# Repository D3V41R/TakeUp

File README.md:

# TakeUp

**TakeUp** is a custom quadrotor flight stack built from scratch: a hand-wired STM32F4 flight controller, a self-etched power distribution board, a bit-banged NRF24L01+ radio link, and a from-scratch DShot150 ESC driver. The end goal is voice-controlled flight — commands transmitted over audio instead of a stick input — with the current build flying on a manual PS5-controller-over-RF link while the audio pipeline is developed.

> **Status: in progress.** Attitude estimation, the RF link, and standard PWM motor control are working. DShot150 and voice control are active work-in-progress (see [Known Limitations](#known-limitations--todo)).

---

## Table of Contents

- [System Overview](#system-overview)
- [Repository Layout](#repository-layout)
- [Flight Controller (STM32F4)](#flight-controller-stm32f4)
- [IMU / Attitude Estimation (MPU6050)](#imu--attitude-estimation-mpu6050)
- [Wireless Link (NRF24L01+)](#wireless-link-nrf24l01)
- [Motor Control](#motor-control)
- [Custom DShot150 Driver](#custom-dshot150-driver)
- [Power Distribution Board](#power-distribution-board)
- [Building the Firmware](#building-the-firmware)
- [Known Limitations / TODO](#known-limitations--todo)
- [License](#license)

---

## System Overview

Today, the RC packet source is a PS5 controller relayed through an ESP32 (`Software/Src/esp32.c`) rather than voice — this is the interim control path used to validate the flight controller, IMU fusion, and radio link while the voice front-end is built out.

---

## Repository Layout

```
TakeUp/
├── Hardware/
│   └── BMS/
│       ├── DroneBMS.kicad_sch     # power distribution board schematic (KiCad 9)
│       ├── DroneBMS.kicad_pcb     # 4-layer PCB layout
│       └── PCB_Render_1.png       # 3D render
│   └── Flight Controller/
│       └── IMG_4678.jpeg          # hand-soldered flight controller build
├── Software/
│   ├── INC/                       # headers
│   │   ├── Dshot150.h
│   │   ├── Motors.h
│   │   ├── Nrf2401.h
│   │   ├── mpu6050.h
│   │   └── main.h
│   └── Src/
│       ├── Dshot150.c              # custom DShot150 frame builder + DMA-PWM transmit
│       ├── Motors.c                # standard 1000-2000us PWM ESC control
│       ├── Nrf2401.c                # bare-register NRF24L01+ driver (no external RF24 lib)
│       ├── mpu6050.c                # IMU driver + complementary filter
│       ├── esp32.c                  # ESP32 transmitter sketch (PS5 controller → NRF24)
│       └── main.c                   # flight controller entry point / RX loop
└── image.png                        # power board schematic export
```

---

## Flight Controller (STM32F4)

The flight controller runs on an STM32F4 Nucleo-64 board (pin map matches the standard Nucleo layout: `PC13` user button, `PA5` = `LD2`). Firmware is generated with STM32CubeMX/HAL and hand-extended.

*Hand-wired prototype: MPU6050 breakout and NRF24L01+ (with SMA antenna) soldered onto perfboard with screw-terminal breakouts for power and signal.*

**Clock tree:** 8 MHz HSE → PLL (`M=4, N=72, P=/2`) → 72 MHz SYSCLK, APB1 = 36 MHz (72 MHz timer clock), APB2 = 72 MHz.

**Peripherals in use:**

| Peripheral | Role | Pins |
|---|---|---|
| `I2C1` | MPU6050 IMU, 100 kHz standard mode | `PB6` = SCL, `PB7` = SDA |
| `SPI2` | NRF24L01+ radio, mode 0, `fPCLK/2` | `PB14` = MISO, `PB15` = MOSI, `PC7` = SCK |
| — | NRF24 chip-select / chip-enable (bit-banged GPIO, not SPI NSS) | `PC0` = CSN, `PB0` = CE |
| `TIM2` (4ch) | ESC PWM / DShot output | `PA0` = CH1 (active), `PA1` = CH2, `PB10` = CH3, `PB2` = CH4 (configured, unused) |
| `USART2` | Debug/telemetry console, 115200 8N1 | `PA2` = TX, `PA3` = RX |

Boot sequence (`main.c`): GPIO → USART2 → I2C1 → SPI2 → TIM2 → arm ESC (`Motor_Init`) → bring up radio (`Nrf_init`) → enter RX loop, printing `BOOT`/`I2C OK`/`SPI OK`/`TIM OK` over UART at each stage so a bring-up failure is localized immediately from the serial log.

---

## IMU / Attitude Estimation (MPU6050)

`mpu6050.c` talks to the MPU6050 directly over `I2C1` (no external library) at address `0x68`.

**Init sequence:**

| Register | Value | Purpose |
|---|---|---|
| `0x75` (`WHO_AM_I`) | read, expect `0x68` | sanity check on boot |
| `0x6B` (`PWR_MGMT_1`) | `0x00` | wake from sleep, select internal clock |
| `0x1A` (`CONFIG`) | `0x01` | DLPF on, ~184 Hz bandwidth |
| `0x25` (`SMPLRT_DIV`) | `0x00` | sample rate = 1 kHz / (1 + 0) = 1 kHz |
| `0x1B` (`GYRO_CONFIG`) | `0b00011000` | ±2000 °/s full scale |
| `0x1C` (`ACCEL_CONFIG`) | `0x00` | ±16 g full scale |

Raw accel/gyro burst-reads come from `0x3B` (6 bytes, accel X/Y/Z) and `0x43` (6 bytes, gyro X/Y/Z), scaled by the datasheet sensitivity for the selected range (`/16384.0f` g/LSB for accel, `/16.4f` (°/s)/LSB for gyro).

**Gyro calibration** (`calibrate_gyro`) averages 1000 samples at boot to compute a static bias — currently computed but not yet subtracted from live readings (see [Known Limitations](#known-limitations--todo)).

**Attitude fusion** (`log_data`) runs a single-stage complementary filter:

1. Exponential low-pass (`ALPHA = 0.02`) on both accel and gyro channels.
2. Body-rate → Euler-rate transform: `phiHat_rps = gx + tan(theta)*(sin(phi)*gy + cos(phi)*gz)`, `thetaHat_rps = cos(phi)*gy - sin(phi)*gz`.
3. Gyro integration at `dt = 0.001 s` (1 kHz loop assumption) added to the running angle.
4. Fusion with accel-derived tilt (`atan`/`asin` off the gravity vector) at a 0.98 / 0.05 gyro/accel blend, printed over `USART2` as `Pitch:__, Roll:__`.

---

## Wireless Link (NRF24L01+)

Both ends of the radio link are custom drivers — the STM32 side (`Nrf2401.c`) talks directly to the NRF24L01+ command/register set over `SPI2` with no radio library, and the transmit side (`esp32.c`) uses the Arduino `RF24` library on an ESP32 paired to a PS5 controller over Bluetooth.

**Link configuration (must match on both ends):**

| Setting | Value |
|---|---|
| Data rate | 1 Mbps |
| RF channel | 85 (2.485 GHz) |
| TX power | 0 dBm |
| Address width | 5 bytes (`SETUP_AW = 0x03`) |
| RX/TX address | `E7 E7 E7 E7 E7` |
| Payload size | 16 bytes, static (no dynamic payloads) |
| Auto-ACK | disabled on both ends |
| CRC | 16-bit (ESP32 side); STM32 driver disables hardware auto-ack/CRC handling and relies on the fixed packet contract instead |

**Packet format** — a flat 16-byte struct sent as raw bytes:

```c
typedef struct {
    float throttle;
    float roll;
    float pitch;
    float yaw;
} rc_packet;   // 4 x 4-byte float = 16 bytes, matches NRF24 payload size exactly
```

**TX side** (`esp32.c`): reads PS5 gamepad stick axes via `ps5Controller`, maps left stick → throttle/roll and right stick → pitch/yaw, and pushes a packet over `RF24::write()` roughly every 20 ms.

**RX side** (`Nrf2401.c` + `main.c`): `Nrf_init()` powers up the radio, configures the RF settings above, and starts listening (`CE` high). `Recieve_nrf()` polls the `STATUS` register for the `RX_DR` flag, pulls the 16-byte payload with the `R_RX_PAYLOAD` command, and clears the flag. `main.c` copies the payload into an `rc_packet`, runs the throttle channel through a first-order low-pass (`alpha = 0.1`), and feeds the result to `Motor_SetSpeed()`.

Note: `enable_auto_ack()` exists in the driver but is not currently called from `Nrf_init()` — auto-ack stays disabled to match the transmitter's `setAutoAck(false)`.

---

## Motor Control

`Motors.c` drives ESCs with standard hobby PWM on `TIM2` channel 1: with the timer clocked at 1 MHz (72 MHz / (prescaler 71 + 1)) and a 20000-tick period, `CCR1` directly represents the pulse width in **microseconds** at a 50 Hz refresh rate — the same 1000–2000 µs framing every analog PWM ESC expects.

| Function | Behavior |
|---|---|
| `Motor_Init()` | Arms the ESC: full throttle (2000) for 2 s, then minimum (1000) for 2 s, matching the standard ESC calibration/arm beep sequence |
| `Motor_SetSpeed(percent)` | Maps 0–100 % linearly to 1000–2000 µs |
| `Motor_SetRaw(ccr)` | Direct CCR write for bench testing |
| `Motor_Stop()` | Forces minimum throttle (1000) |
| `Motor_Control_UART()` | Serial bench-test command parser (`S<pct>` set speed, `R<ccr>` set raw, `X` stop) over `USART2` |

Only `TIM2_CH1` is currently wired to a motor output in `main.c` — channels 2–4 are configured (see pin table above) but not yet driven, so multi-motor mixing isn't implemented yet.

---

## Custom DShot150 Driver

`Dshot150.c` implements the DShot150 digital ESC protocol frame-by-frame, from scratch, on top of `TIM2` + DMA.

**Frame construction is spec-correct.** A DShot frame is 16 bits: 11-bit throttle value, 1 telemetry-request bit, and a 4-bit CRC:

```c
data  = (throttle << 1) | telemetry;                  // 12 bits: 11-bit throttle + telemetry
crc   = (data ^ (data >> 4) ^ (data >> 8)) & 0xF;      // XOR-nibble checksum, per the DShot spec
frame = (data << 4) | crc;                             // final 16-bit frame
```

**Bit encoding.** Each of the 16 frame bits is expanded into a duty-cycle value for one PWM period — `170` (≈85% duty) for a `1` bit, `85` (≈42.5% duty) for a `0` bit — into a 17-entry buffer (16 bits + a trailing `0` to force the line low/reset). The buffer is streamed to `TIM2_CH1`'s `CCR1` register via `HAL_TIM_PWM_Start_DMA`, so each bit's duty cycle loads automatically without CPU intervention.

```c
void readBits(uint16_t data) {
    for (int i = 0; i < 16; i++) {
        uint16_t bitVal = (data >> (15 - i)) & 0x1;
        dshotbuffer[i] = bitVal ? 170 : 85;
    }
    dshotbuffer[16] = 0;
}
```

**Current state:** this correctly reproduces DShot's *bit encoding and checksum*, but the timer feeding it is still configured for the 20 ms / 1 MHz standard-PWM setup described above rather than a proper DShot150 bit clock (real DShot150 needs a ~6.67 µs bit period, i.e. the whole 16-bit frame takes ~107 µs — not 16 × 20 ms). Getting this fully protocol-compliant means giving `TIM2` a dedicated ARR/prescaler for DShot bit timing (or moving DShot to its own timer) and reworking the DMA burst length accordingly. This is the main piece marked "in progress" in this repo — see below.

---

## Power Distribution Board

`Hardware/BMS/DroneBMS.kicad_sch` — titled **"TakeUp Power Distribution Board"** in the schematic sheet — is a custom 4-layer (1.6 mm) PCB that takes a 3S LiPo in over an XT60 connector and produces the regulated rails and battery telemetry the flight controller needs. It's referred to informally as the "BMS" but its scope today is power conditioning + voltage sensing rather than active cell balancing.

**Power path:**

```
XT60 (3S, ~11.1V) → Fuse (F1) + TVS diode (D3, SMAJ15A) → VBATTMAIN
                                                              │
                              ┌───────────────────────────────┼───────────────────────────────┐
                              ▼                                ▼                               ▼
                    LMR51430 buck (U1)                4x ESC power pads                Battery-voltage
                    11.1V → 5V, 4.7uH inductor,        (raw VBATTMAIN + GND,            sense divider
                    73k/10k feedback divider           470uF bulk cap each)             (10k/3.3k → STM32 ADC)
                              │
                              ▼
                    AMS1117-3.3 LDO (U2)
                    5V → 3.3V logic rail
```

| Section | Components | Notes |
|---|---|---|
| Battery input | `XT60BATT1`, `F1` (fuse), `D3` (SMAJ15A TVS) | Overcurrent + transient surge protection on the main battery line before it fans out |
| 5V rail | `U1` LMR51430 synchronous buck, `L1` 4.7 µH, `R1`/`R2` = 73k/10k feedback, bulk + decoupling caps, `D1` "5V On" LED | Steps 11.1V pack voltage down to 5V |
| 3.3V rail | `U2` AMS1117-3.3 LDO, `D2` "3.3V On" LED | Steps 5V down to 3.3V for the MCU/logic |
| Battery sense | `R3`/`R4` = 10k/3.3k divider → `J1`/`J2` | Scales VBATTMAIN down into ADC range for the STM32 to read pack voltage in software |
| ESC power | `ESC1`–`ESC4` pads, 470 µF bulk cap each, plus a raw +12V pad | Distributes unregulated battery voltage directly to each ESC |

Board: 4 copper layers (`F.Cu`/`In1.Cu`/`In2.Cu`/`B.Cu`), 1.6 mm stack-up, 4 mounting holes, KiCad 9 source files included for both schematic and layout, plus a 3D render at `Hardware/BMS/PCB_Render_1.png`.

---

## Building the Firmware

The `Software/` tree is a standard STM32CubeIDE / STM32CubeMX HAL project targeting an STM32F4 Nucleo-64 board.

1. Import `Software/` into STM32CubeIDE (or point a Makefile-based ARM GCC toolchain at `Software/INC` and `Software/Src`).
2. Flash over the Nucleo's onboard ST-LINK.
3. Open a serial terminal at 115200 8N1 on the ST-LINK VCP to watch boot status (`BOOT`, `I2C OK`, `SPI OK`, `TIM OK`) and the live RC/attitude log.
4. Flash `Software/Src/esp32.c` to an ESP32 (Arduino core, `RF24` + `ps5Controller` libraries) to act as the transmitter, or drive `TIM2_CH1` directly via `Motor_Control_UART()` for a bench test with no radio at all.

---

## Known Limitations / TODO

- **Voice control isn't implemented yet.** The current transmit path is a PS5 controller relayed through an ESP32, standing in for the audio pipeline this project is ultimately meant to use.
- **Power board has no active cell balancing/protection IC** — today it's fusing, a TVS clamp, regulation, and voltage-divider telemetry, not a full smart BMS.

---

## License

MIT — see [LICENSE](LICENSE).

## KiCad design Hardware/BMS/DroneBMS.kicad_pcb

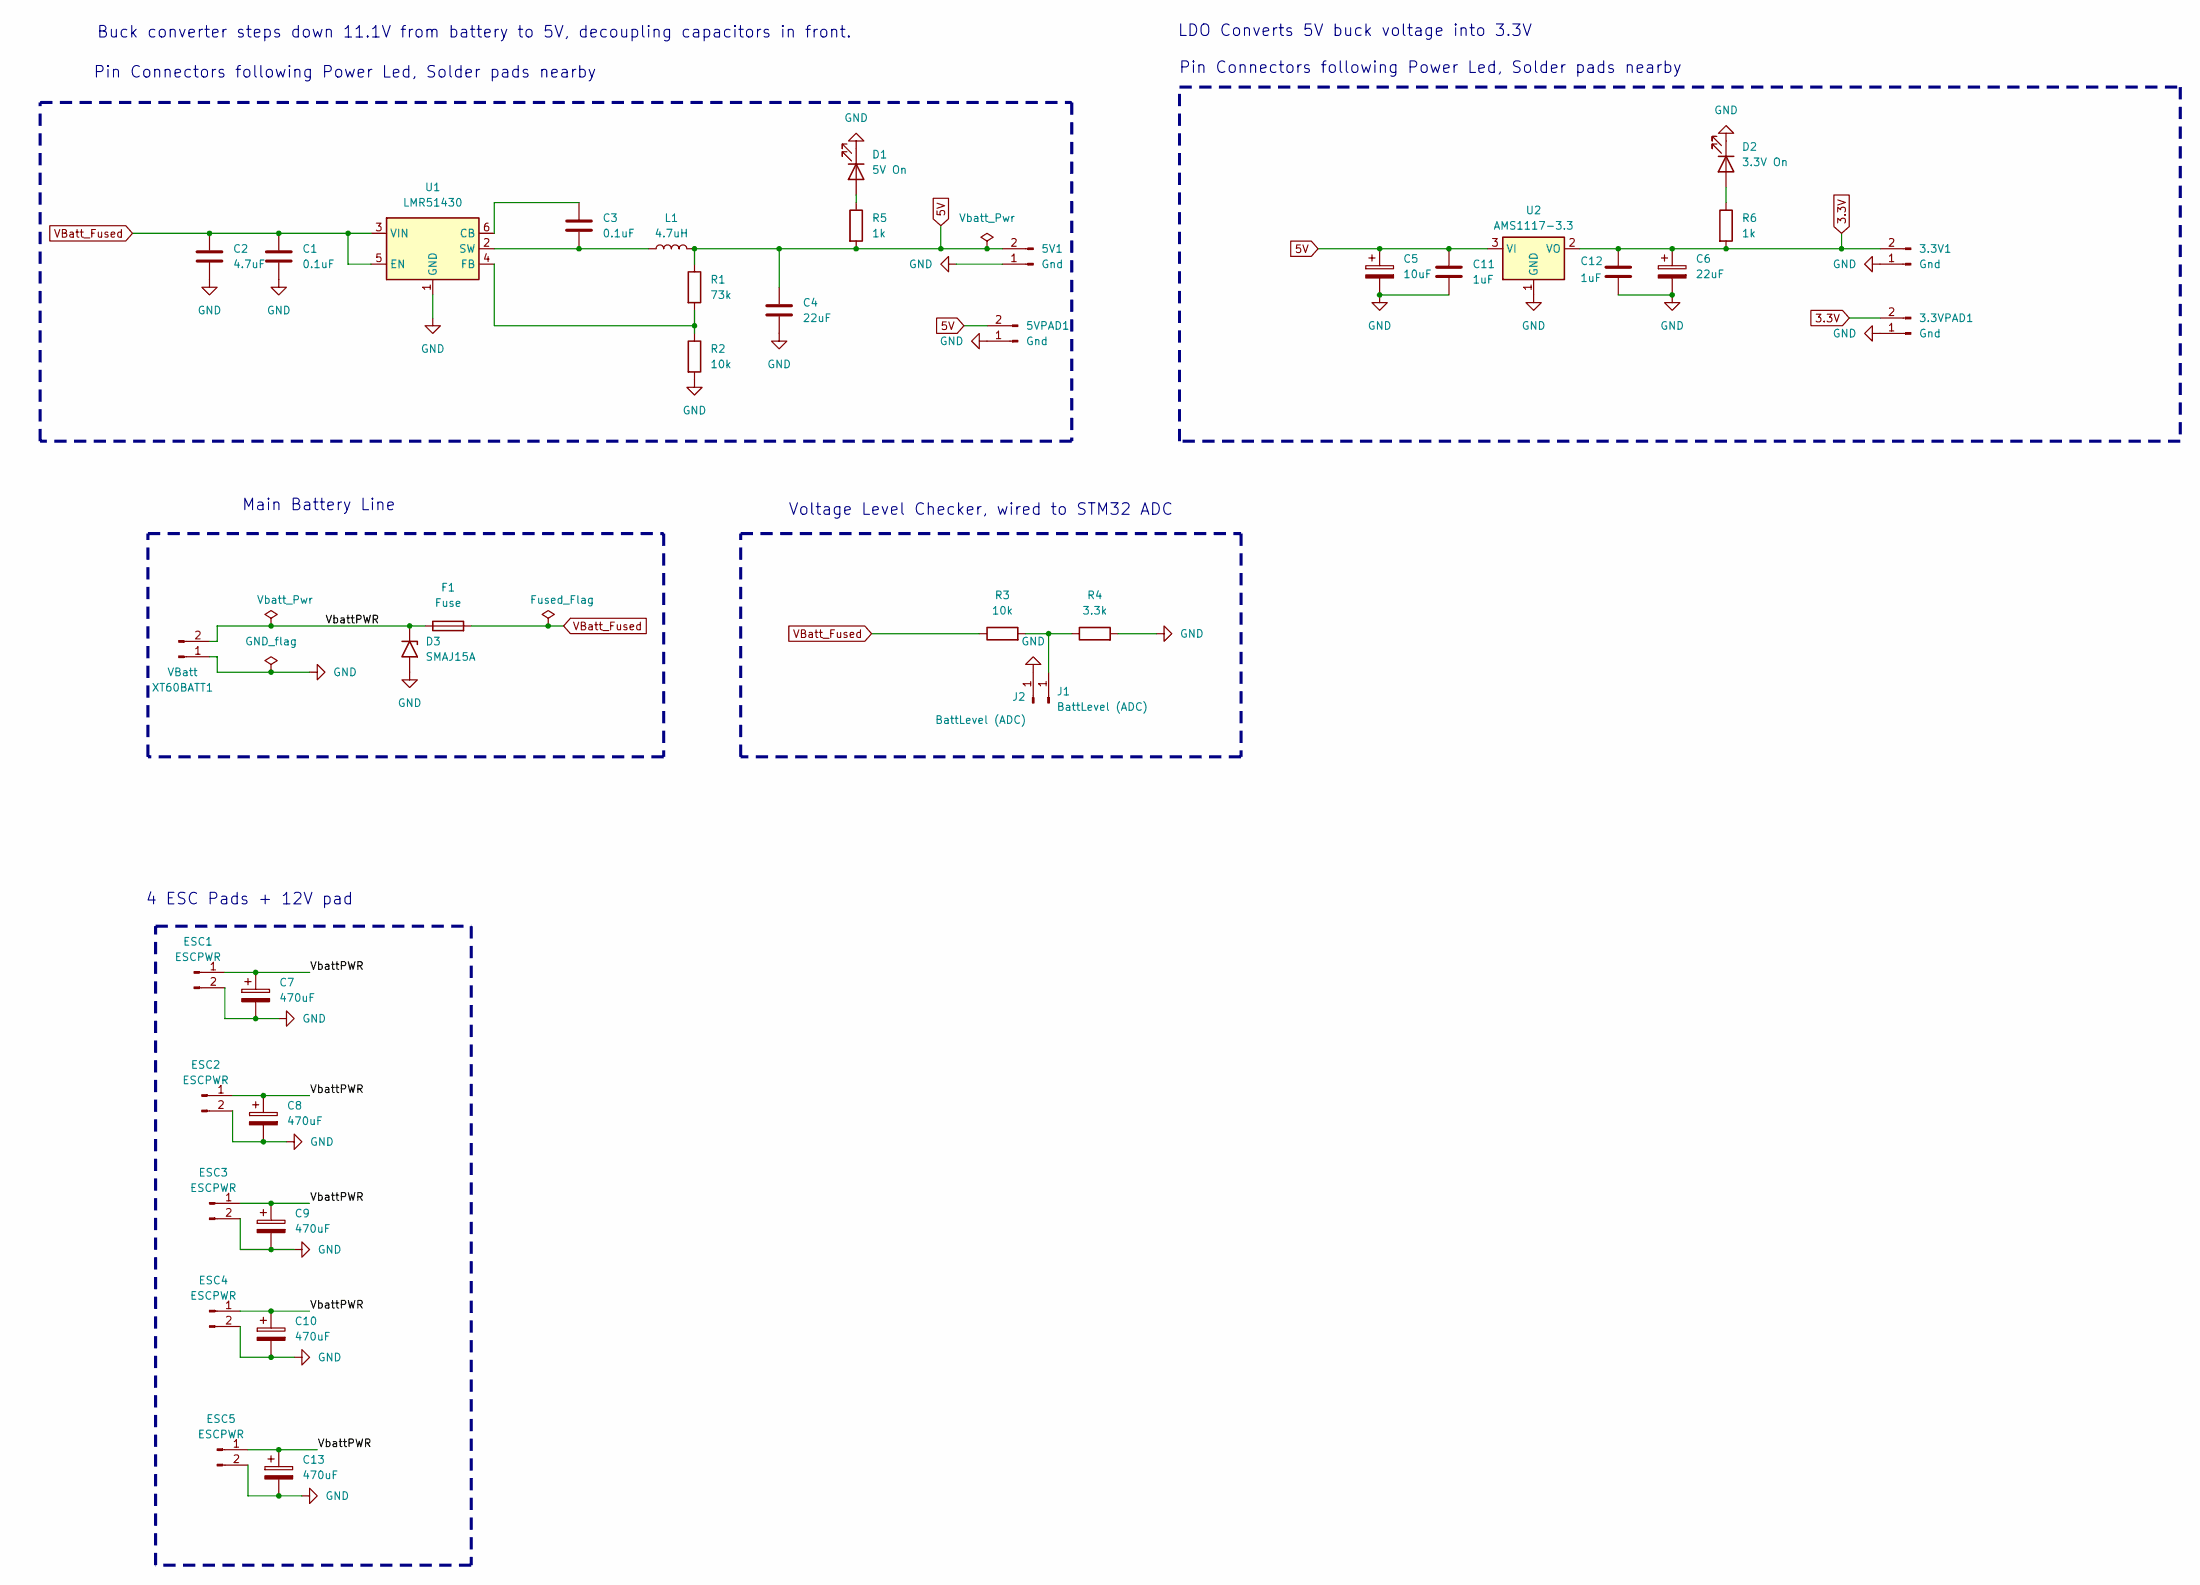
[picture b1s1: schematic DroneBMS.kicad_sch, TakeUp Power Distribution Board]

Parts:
3.3V1, 5V1: Gnd; PinHeader_1x02_P2.54mm_Vertical
3.3VPAD1, 5VPAD1: Gnd; ESC_SOLDER_PAD
C1, C3: 0.1uF; C_1206_3216Metric
C2: 4.7uF; C_1206_3216Metric
C4: 22uF; C_1206_3216Metric
C5: 10uF; CP_Elec_4x4.5
C6: 22uF; CP_Elec_4x5.3
C7, C8, C9, C10, C13: 470uF; CP_Radial_D8.0mm_P3.50mm
C11, C12: 1uF; C_1206_3216Metric
D1: 5V On; LED_0805_2012Metric
D2: 3.3V On; LED_0805_2012Metric
D3: SMAJ15A; D_SMA
ESC1, ESC2, ESC3, ESC4, ESC5: ESCPWR; ESC_SOLDER_PAD
F1: Fuse; Fuse_1206_3216Metric
J1, J2: BattLevel (ADC); PinHeader_1x01_P1.00mm_Vertical
L1: 4.7uH; IND_VSAB0630-4R7M
R1: 73k; R_0805_2012Metric
R2, R3: 10k; R_0805_2012Metric
R4: 3.3k; R_0805_2012Metric
R5, R6: 1k; R_0805_2012Metric
U1: LMR51430; SOT-23-6
U2: AMS1117-3.3; SOT-223-3_TabPin2
XT60BATT1: VBatt; AMASS_XT60-M_1x02_P7.20mm_Vertical

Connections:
3.3V: 3.3V1.2, 3.3VPAD1.2, C6.1, C12.1, R6.2, U2.2 (VO)
5V: 5V1.2, 5VPAD1.2, C4.1, C5.1, C11.1, L1.2, R1.1, R5.2, U2.3 (VI)
/VbattPWR: C7.1, C8.1, C9.1, C10.1, C13.1, D3.1 (A1), ESC1.1, ESC2.1, ESC3.1, ESC4.1, ESC5.1, F1.1, XT60BATT1.2
GND: 3.3V1.1, 3.3VPAD1.1, 5V1.1, 5VPAD1.1, C1.2, C2.2, C4.2, C5.2, C6.2, C7.2, C8.2, C9.2, C10.2, C11.2, C12.2, C13.2, D1.1 (K), D2.1 (K), D3.2 (A2), ESC1.2, ESC2.2, ESC3.2, ESC4.2, ESC5.2, J2.1, R2.2, R4.2, U1.1 (GND), U2.1 (GND), XT60BATT1.1
unnamed: D1.2 (A), R5.1
unnamed: D2.2 (A), R6.1
unnamed: J1.1, R3.2, R4.1
unnamed: C3.1, U1.6 (CB)
unnamed: R1.2, R2.1, U1.4 (FB)
unnamed: C3.2, L1.1, U1.2 (SW)
VBatt_Fused: C1.1, C2.1, F1.2, R3.1, U1.3 (VIN), U1.5 (EN)

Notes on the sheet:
Voltage Level Checker, wired to STM32 ADC
Buck converter steps down 11.1V from battery to 5V, decoupling capacitors in front.
LDO Converts 5V buck voltage into 3.3V
Pin Connectors following Power Led, Solder pads nearby
Main Battery Line
4 ESC Pads + 12V pad

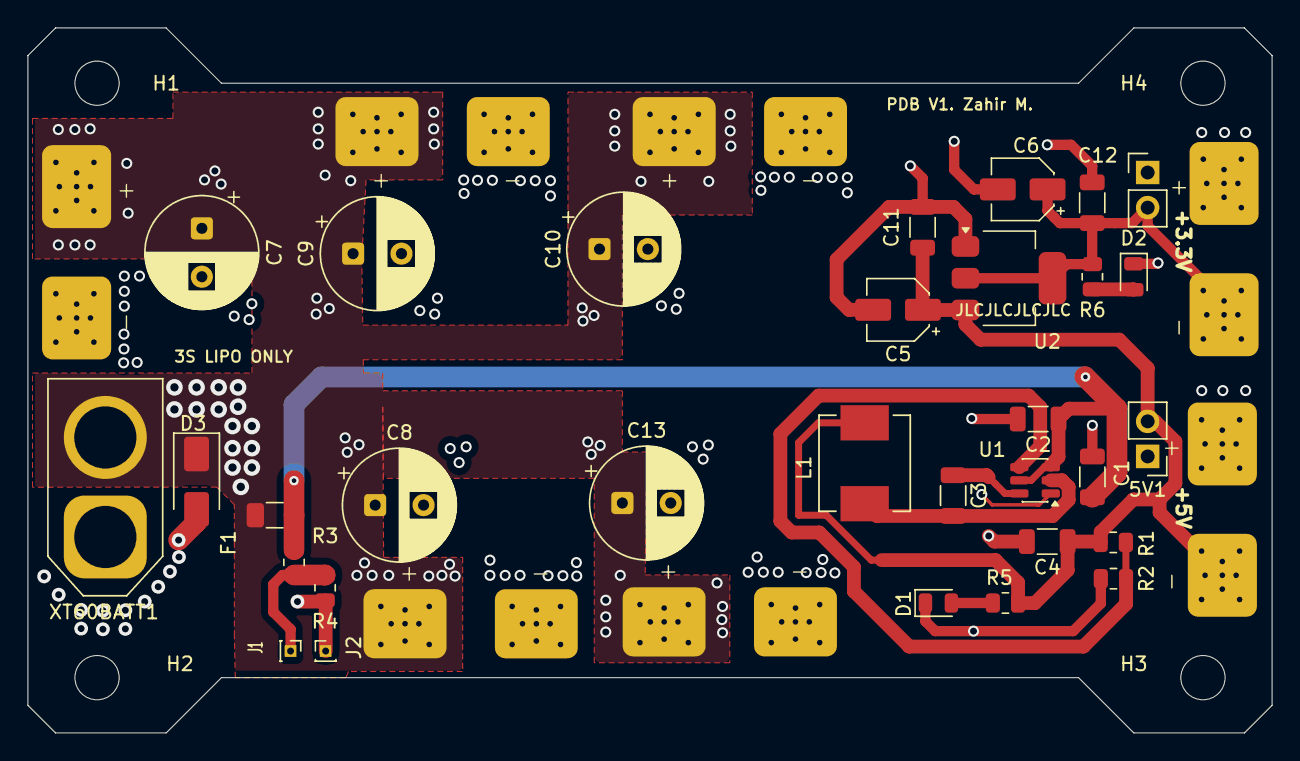
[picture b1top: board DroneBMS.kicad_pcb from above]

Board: 4 copper layers, 90.0 x 51.0 mm, 42 parts (0 on the bottom side), 11 nets.

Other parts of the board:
H1, H2, H3, H4: MountingHole_3.2mm_M3

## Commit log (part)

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2026-06-12 Added Software files for Mpu sensor calibration
    * Implemented Complimentary filter to determine accurate Roll / Pitch Angles
2026-06-21 Added Motor Control, RF Recieving And Transmission, Filtered Motor Control
    *Added configurable Motor control Via Tim2 Peripheral
    * Added NRF recieving and transmission on dedicated address
    * Configured and tested drone Payload for Roll / Pitch / Yaw / Throttle
2026-06-23 Added Esp32 Transmitter Code
2026-06-25 Added Kicad Schematic
2026-06-28 Added BMS Design Files
2026-06-28 Updated Pcb Footprints
